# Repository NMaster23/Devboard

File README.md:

__Devboard__

A devboard for the Stasis YSWS event based on the Devboard starter project.

Finished Schematic:

Starting PCB:

Finished PCB:

Expected Production Unit:

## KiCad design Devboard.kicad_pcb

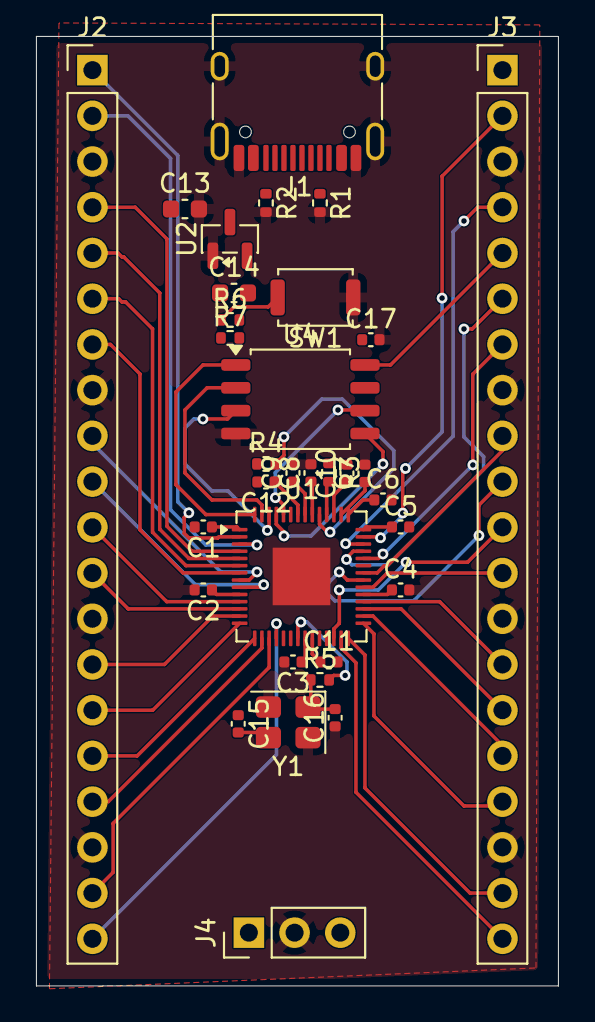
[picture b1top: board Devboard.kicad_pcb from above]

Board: 2 copper layers, 29.0 x 52.8 mm, 33 parts (0 on the bottom side), 53 nets.

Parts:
C1, C10: 1uF; C_0402_1005Metric
C2, C3, C4, C5, C6, C7, C8, C9, C11, C12, C17: 0.1uF; C_0402_1005Metric
C13, C14: 10uF; C_0603_1608Metric
C15, C16: 33pF; C_0402_1005Metric
J1: USB_C_Receptacle_USB2.0_14P; USB_C_Receptacle_HRO_TYPE-C-31-M-12
J2, J3: Conn_01x20_Pin; PinHeader_1x20_P2.54mm_Vertical
J4: Conn_01x03_Pin; PinHeader_1x03_P2.54mm_Vertical
R1, R2: 5.1K; R_0402_1005Metric
R3, R4: 27; R_0402_1005Metric
R5, R6: 1K; R_0402_1005Metric
R7: 10K; R_0402_1005Metric
SW1: SW_Push; SW_Push_SPST_NO_Alps_SKRK
U1: RP2040; QFN-56-1EP_7x7mm_P0.4mm_EP3.2x3.2mm
U2: MCP1700x-330xxTT; SOT-23
U4: W25Q128JVS; SOIC-8_5.3x5.3mm_P1.27mm
Y1: 12 MHz; Crystal_SMD_3225-4Pin_3.2x2.5mm

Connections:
+1V1: C10.1, C11.1, C12.1, U1.23 (DVDD), U1.45 (VREG_VOUT), U1.50 (DVDD)
+3V3: C1.1, C2.1, C3.1, C4.1, C5.1, C6.1, C7.1, C8.1, C9.1, C14.1, C17.1, J3.5, R7.2, U1.1 (IOVDD), U1.10 (IOVDD), U1.22 (IOVDD), U1.33 (IOVDD), U1.42 (IOVDD), U1.43 (ADC_AVDD), U1.44 (VREG_VIN), U1.48 (USB_VDD), U1.49 (IOVDD), U2.2 (VO), U4.8 (VCC)
GND: C1.2, C2.2, C3.2, C4.2, C5.2, C6.2, C7.2, C8.2, C9.2, C13.2, C14.2, C15.1, C16.1, C17.2, J1.A1 (GND), J1.A12 (GND), J1.B1 (GND), J1.B12 (GND), J1.SH (SHIELD), J2.3, J2.8, J2.13, J2.18, J3.3, J3.8, J3.13, J3.18, J4.2, R1.2, R2.2, SW1.1, U1.19 (TESTEN), U1.57 (GND), U2.1 (GND), U4.4 (GND), Y1.2 (G), Y1.4 (G)
GPIO0: J2.1, U1.2 (GPIO0)
GPIO1: J2.2, U1.3 (GPIO1)
GPIO2: J2.4, U1.4 (GPIO2)
GPIO3: J2.5, U1.5 (GPIO3)
GPIO4: J2.6, U1.6 (GPIO4)
GPIO5: J2.7, U1.7 (GPIO5)
GPIO6: J2.9, U1.8 (GPIO6)
GPIO7: J2.10, U1.9 (GPIO7)
GPIO8: J2.11, U1.11 (GPIO8)
GPIO9: J2.12, U1.12 (GPIO9)
GPIO10: J2.14, U1.13 (GPIO10)
GPIO11: J2.15, U1.14 (GPIO11)
GPIO12: J2.16, U1.15 (GPIO12)
GPIO13: J2.17, U1.16 (GPIO13)
GPIO14: J2.19, U1.17 (GPIO14)
GPIO15: J2.20, U1.18 (GPIO15)
GPIO16: J3.20, U1.27 (GPIO16)
GPIO17: J3.19, U1.28 (GPIO17)
GPIO18: J3.17, U1.29 (GPIO18)
GPIO19: J3.16, U1.30 (GPIO19)
GPIO20: J3.15, U1.31 (GPIO20)
GPIO21: J3.14, U1.32 (GPIO21)
GPIO22: J3.12, U1.34 (GPIO22)
GPIO23: J3.10, U1.35 (GPIO23)
GPIO24: J3.9, U1.36 (GPIO24)
GPIO26_ADC0: J3.7, U1.38 (GPIO26/ADC0)
GPIO27_ADC1: J3.6, U1.39 (GPIO27/ADC1)
GPIO28_ADC2: J3.4, U1.40 (GPIO28/ADC2)
GPIO29_ADC3: J3.2, U1.41 (GPIO29/ADC3)
unnamed: C10.2, C11.2, C12.2
unnamed: C16.2, R5.1, Y1.1
unnamed: J1.A5 (CC1), R1.1
unnamed: J1.B5 (CC2), R2.1
unnamed: R6.1, SW1.2
unnamed: R3.2, U1.46 (USB_DM)
unnamed: R4.2, U1.47 (USB_DP)
QSPI_SCLK: U1.52 (QSPI_SCLK), U4.6 (CLK)
QSPI_SD0: U1.53 (QSPI_SD0), U4.5 (DI/IO_{0})
QSPI_SD1: U1.55 (QSPI_SD1), U4.2 (DO/IO_{1})
QSPI_SD2: U1.54 (QSPI_SD2), U4.3 (~WP/IO_{2})
QSPI_SD3: U1.51 (QSPI_SD3), U4.7 (~HOLD/~RESET/IO_{3})
QSPI_SS: R6.2, R7.1, U1.56 (~QSPI_SS), U4.1 (~CS)
RUN: J3.11, U1.26 (RUN)
SWCLK: J4.1, U1.24 (SWCLK)
SWD: J4.3, U1.25 (SWDIO)
USB_D+: J1.A6 (D+), J1.B6 (D+), R4.1
USB_D-: J1.A7 (D-), J1.B7 (D-), R3.1
VBUS: C13.1, J1.A4 (VBUS), J1.A9 (VBUS), J1.B4 (VBUS), J1.B9 (VBUS), J3.1, U2.3 (VI)
XIN: C15.2, U1.20 (XIN), Y1.3
XOUT: R5.2, U1.21 (XOUT)

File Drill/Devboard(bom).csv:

Reference,Qty,Value,DNP,Exclude from BOM,Exclude from Board,Footprint,Datasheet
"C1,C10",2,1uF,,,,Capacitor_SMD:C_0402_1005Metric,
"C2,C3,C4,C5,C6,C7,C8,C9,C11,C12,C17",11,0.1uF,,,,Capacitor_SMD:C_0402_1005Metric,
"C13,C14",2,10uF,,,,Capacitor_SMD:C_0603_1608Metric,
"C15,C16",2,33pF,,,,Capacitor_SMD:C_0402_1005Metric,
J1,1,USB_C_Receptacle_USB2.0_14P,,,,Connector_USB:USB_C_Receptacle_HRO_TYPE-C-31-M-12,https://www.usb.org/sites/default/files/documents/usb_type-c.zip
"J2,J3",2,Conn_01x20_Pin,,,,Connector_PinHeader_2.54mm:PinHeader_1x20_P2.54mm_Vertical,
J4,1,Conn_01x03_Pin,,,,Connector_PinHeader_2.54mm:PinHeader_1x03_P2.54mm_Vertical,
"R1,R2",2,5.1K,,,,Resistor_SMD:R_0402_1005Metric,
"R3,R4",2,27,,,,Resistor_SMD:R_0402_1005Metric,
"R5,R6",2,1K,,,,Resistor_SMD:R_0402_1005Metric,
R7,1,10K,,,,Resistor_SMD:R_0402_1005Metric,
SW1,1,SW_Push,,,,Button_Switch_SMD:SW_Push_SPST_NO_Alps_SKRK,
U1,1,RP2040,,,,Package_DFN_QFN:QFN-56-1EP_7x7mm_P0.4mm_EP3.2x3.2mm,https://datasheets.raspberrypi.com/rp2040/rp2040-datasheet.pdf
U4,1,W25Q128JVS,,,,Package_SO:SOIC-8_5.3x5.3mm_P1.27mm,https://www.winbond.com/resource-files/w25q128jv_dtr%20revc%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
U2,1,MCP1700x-330xxTT,,,,Package_TO_SOT_SMD:SOT-23,http://ww1.microchip.com/downloads/en/DeviceDoc/20001826D.pdf
Y1,1,12 MHz,,,,Crystal:Crystal_SMD_3225-4Pin_3.2x2.5mm,

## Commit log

2026-04-19 Created README.md
2026-04-19 Delete Devboard-pnp_top.gbr
    Repository Cleanup
2026-04-19 Delete Devboard-pnp_bottom.gbr
    Repository Cleanup
2026-04-19 Delete Devboard-bottom-pos.csv
    Repository Cleanup
2026-04-19 Delete Logos.kicad_wks
    Repository Cleanup
2026-04-19 Delete Devboard.kicad_prl
    Repository Cleanup
2026-04-19 Repository Cleanup
    Repository Cleanup
2026-04-19 Repository Assets Additions
    Repository Assets Additions
2026-04-19 Assets Updating
